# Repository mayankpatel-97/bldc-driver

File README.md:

# BLDC Driver

## Overview
This project is an open-source BLDC motor driver designed for drone applications. It implements a sensorless control method using **Back EMF** for efficient and precise motor control.

## Motor Control Methods
There are multiple ways to drive a BLDC motor. The three most common methods are:

1. **Hall Sensor-Based Control**  
   - Uses **hall effect sensors** in the motor to detect rotor position.
   - Suitable for applications requiring high precision.

2. **Back EMF-Based Control (Sensorless)**  
   - Most **common in drone ESCs** (Electronic Speed Controllers).
   - Detects rotor position by measuring **Back EMF voltage** on the floating phase.
   - Eliminates the need for sensors, reducing cost and complexity.

3. **Power Control Mode**  
   - Uses **shunt resistors** to monitor **current in each phase**.
   - Enables precise **torque and power control**.
   - Required for advanced techniques like **Field-Oriented Control (FOC)**.

## Current Implementation
- **Control Method**: Back EMF sensing (sensorless)  
- **Target Application**: Drone ESC

## Future Enhancements
- **CAN Bus Interface** for communication
- **UART Interface** for debugging and configuration
- In the next varient, one board would have the driver for all the 4 motors required for quad copter.

## PCB information 
- Generated gerber files are in gerber folder of the project directory
- PCB file size: 54x29 mm.

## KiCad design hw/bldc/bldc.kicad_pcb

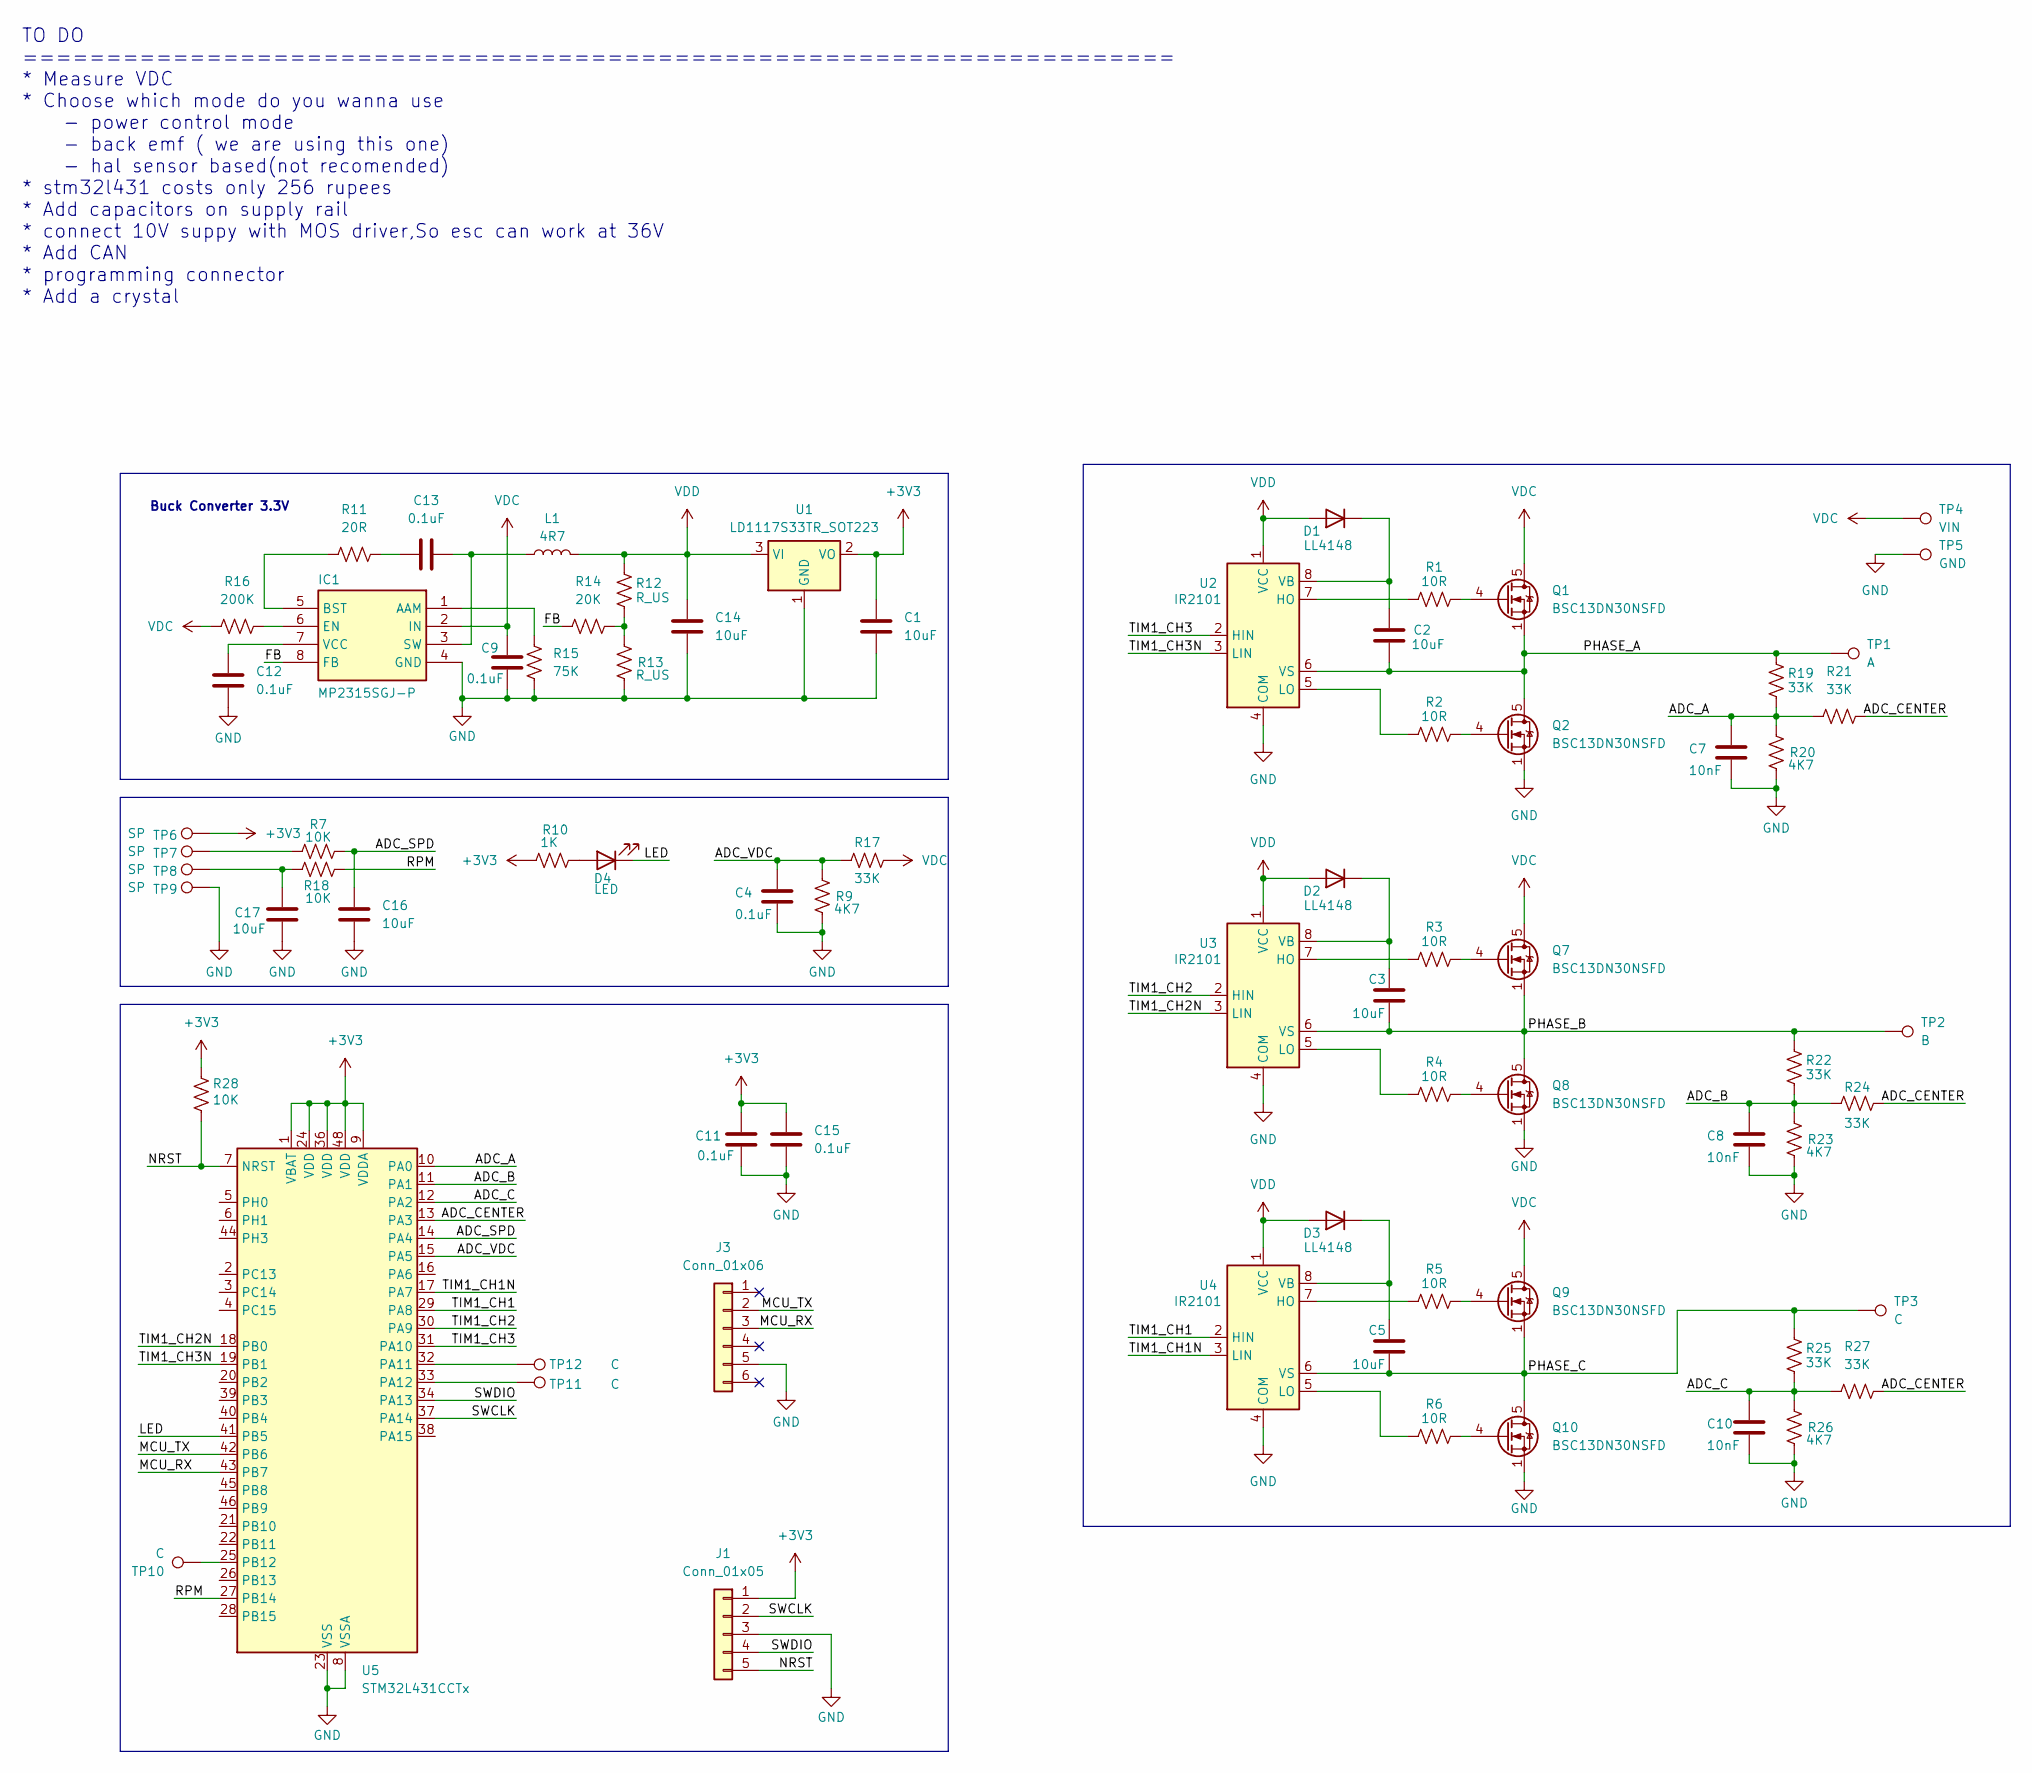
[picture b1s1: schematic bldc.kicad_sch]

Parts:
C1, C2, C3, C5, C14, C16, C17: 10uF; C_0603_1608Metric
C4, C9, C11, C12, C13, C15: 0.1uF; C_0603_1608Metric
C7, C8, C10: 10nF; C_0603_1608Metric
D1, D2, D3: LL4148; D_MiniMELF
D4: LED; LED_0603_1608Metric
IC1: MP2315SGJ-P; MP2315SGJ; Manufacturer_Part_Number MP2315SGJ-P; Mouser Part Number 946-MP2315SGJ-P
J1: Conn_01x05; PinHeader_1x05_P2.00mm_Vertical
J3: Conn_01x06; PinHeader_1x06_P2.54mm_Vertical
L1: 4R7; L_Neosid_SM-PIC0512H
Q1, Q2, Q7, Q8, Q9, Q10: BSC13DN30NSFD; TDSON-8-1
R1, R2, R3, R4, R5, R6: 10R; R_0603_1608Metric
R7, R18, R28: 10K; R_0603_1608Metric
R9, R20, R23, R26: 4K7; R_0603_1608Metric
R10: 1K; R_0603_1608Metric
R11: 20R; R_0603_1608Metric
R12, R13: R_US; R_0603_1608Metric
R14: 20K; R_0603_1608Metric
R15: 75K; R_0603_1608Metric
R16: 200K; R_0603_1608Metric
R17, R19, R21, R22, R24, R25, R27: 33K; R_0603_1608Metric
TP1: A; SOLDERPAD6x4
TP2: B; SOLDERPAD6x4
TP3: C; SOLDERPAD6x4
TP4: VIN; SOLDERPAD6x4
TP5: GND; SOLDERPAD6x4
TP6, TP7, TP8, TP9: SP; TestPoint_Pad_3.0x3.0mm
TP10, TP11, TP12: C; TestPoint_Pad_D1.0mm
U1: LD1117S33TR_SOT223; SOT-223-3_TabPin2
U2, U3, U4: IR2101; SOIC-8_3.9x4.9mm_P1.27mm
U5: STM32L431CCTx; LQFP-48_7x7mm_P0.5mm

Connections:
+3V3: C1.2, C11.2, C15.2, J1.1, R10.1, R28.2, TP6.1, U1.2 (VO), U5.1 (VBAT), U5.9 (VDDA), U5.24 (VDD), U5.36 (VDD), U5.48 (VDD)
/ADC_A: C7.1, R19.2, R20.1, R21.1, U5.10 (PA0)
/ADC_B: C8.1, R22.2, R23.1, R24.1, U5.11 (PA1)
/ADC_C: C10.1, R25.2, R26.1, R27.1, U5.12 (PA2)
/ADC_CENTER: R21.2, R24.2, R27.2, U5.13 (PA3)
/ADC_SPD: C16.2, R18.1, U5.14 (PA4)
/ADC_VDC: C4.1, R9.1, R17.1, U5.15 (PA5)
/FB: IC1.8 (FB), R14.1
/LED: D4.1 (K), U5.41 (PB5)
/MCU_RX: J3.3, U5.43 (PB7)
/MCU_TX: J3.2, U5.42 (PB6)
/NRST: J1.5, R28.1, U5.7 (NRST)
/PHASE_A: C2.2, Q1.1 (S), Q1.2 (S), Q1.3 (S), Q2.5 (D), R19.1, TP1.1, U2.6 (VS)
/PHASE_B: C3.2, Q7.1 (S), Q7.2 (S), Q7.3 (S), Q8.5 (D), R22.1, TP2.1, U3.6 (VS)
/PHASE_C: C5.2, Q9.1 (S), Q9.2 (S), Q9.3 (S), Q10.5 (D), R25.1, TP3.1, U4.6 (VS)
/RPM: R7.1, U5.27 (PB14)
/SWCLK: J1.2, U5.37 (PA14)
/SWDIO: J1.4, U5.34 (PA13)
/TIM1_CH1: U4.2 (HIN), U5.29 (PA8)
/TIM1_CH1N: U4.3 (LIN), U5.17 (PA7)
/TIM1_CH2: U3.2 (HIN), U5.30 (PA9)
/TIM1_CH2N: U3.3 (LIN), U5.18 (PB0)
/TIM1_CH3: U2.2 (HIN), U5.31 (PA10)
/TIM1_CH3N: U2.3 (LIN), U5.19 (PB1)
GND: C1.1, C4.2, C7.2, C8.2, C9.2, C10.2, C11.1, C12.2, C14.1, C15.1, C16.1, C17.1, IC1.4 (GND), J1.3, J3.5, Q2.1 (S), Q2.2 (S), Q2.3 (S), Q8.1 (S), Q8.2 (S), Q8.3 (S), Q10.1 (S), Q10.2 (S), Q10.3 (S), R9.2, R13.2, R15.2, R20.2, R23.2, R26.2, TP5.1, TP9.1, U1.1 (GND), U2.4 (COM), U3.4 (COM), U4.4 (COM), U5.8 (VSSA), U5.23 (VSS), U5.35 (VSS), U5.47 (VSS)
unnamed: C13.1, R11.2
unnamed: C17.2, R7.2, TP8.1
unnamed: C2.1, D1.1 (K), U2.8 (VB)
unnamed: C3.1, D2.1 (K), U3.8 (VB)
unnamed: C5.1, D3.1 (K), U4.8 (VB)
unnamed: D4.2 (A), R10.2
unnamed: IC1.1 (AAM), R15.1
unnamed: IC1.5 (BST), R11.1
unnamed: IC1.6 (EN), R16.2
unnamed: C13.2, IC1.3 (SW), L1.1
unnamed: C12.1, IC1.7 (VCC)
unnamed: Q1.4 (G), R1.2
unnamed: Q2.4 (G), R2.2
unnamed: Q7.4 (G), R3.2
unnamed: Q8.4 (G), R4.2
unnamed: Q9.4 (G), R5.2
unnamed: Q10.4 (G), R6.2
unnamed: R12.2, R13.1, R14.2
unnamed: R18.2, TP7.1
unnamed: R1.1, U2.7 (HO)
unnamed: R2.1, U2.5 (LO)
unnamed: R3.1, U3.7 (HO)
unnamed: R4.1, U3.5 (LO)
unnamed: R5.1, U4.7 (HO)
unnamed: R6.1, U4.5 (LO)
unnamed: TP12.1, U5.32 (PA11)
unnamed: TP11.1, U5.33 (PA12)
unnamed: TP10.1, U5.25 (PB12)
VDC: C9.1, IC1.2 (IN), Q1.5 (D), Q7.5 (D), Q9.5 (D), R16.1, R17.2, TP4.1
VDD: C14.2, D1.2 (A), D2.2 (A), D3.2 (A), L1.2, R12.1, U1.3 (VI), U2.1 (VCC), U3.1 (VCC), U4.1 (VCC)

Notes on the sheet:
TO DO ===================================================================== * Measure VDC * Choose which mode do you wanna use - power control mode - back emf ( we are using this one) - hal sensor based(not recomended) * stm32l431 costs only 256 rupees * Add capacitors on supply rail * connect 10V 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
Buck Converter 3.3V

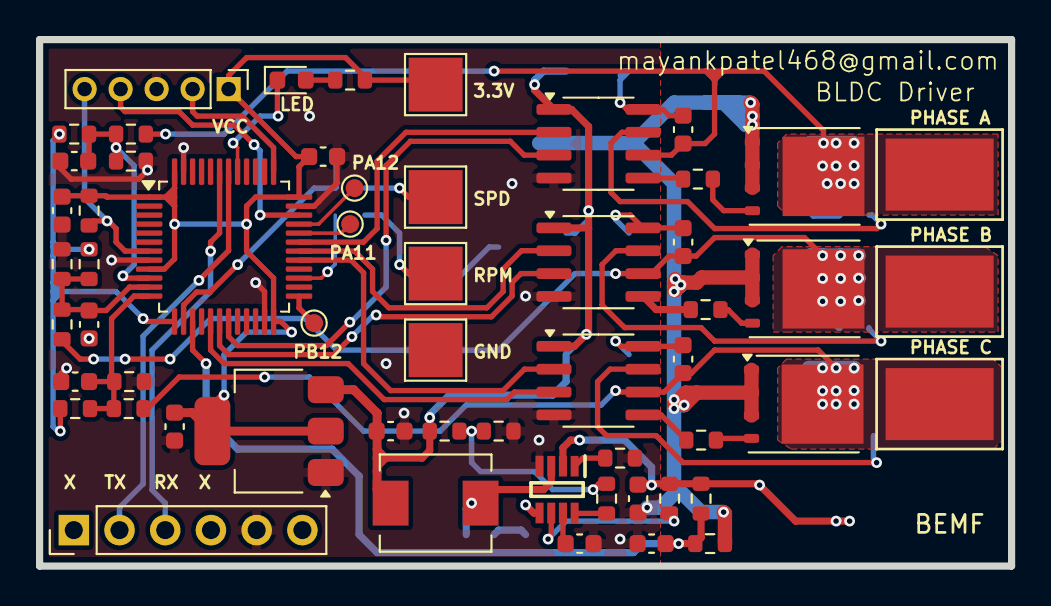
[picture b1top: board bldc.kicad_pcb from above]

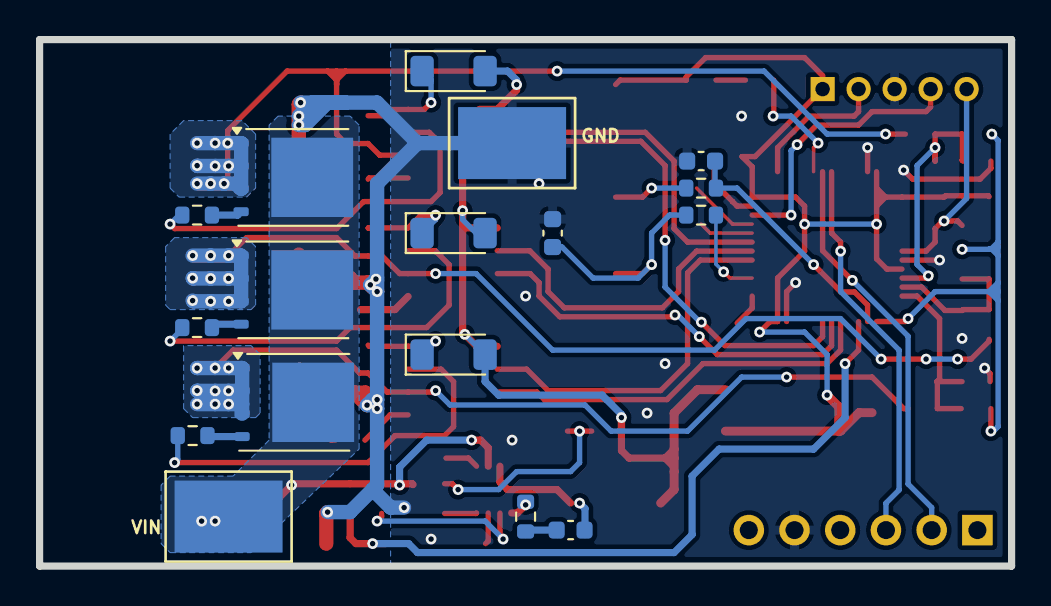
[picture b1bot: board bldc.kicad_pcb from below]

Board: 2 copper layers, 54.0 x 29.2 mm, 74 parts (17 on the bottom side), 55 nets.

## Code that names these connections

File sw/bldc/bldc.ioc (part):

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Mcu.Name=STM32L431C(B-C)Tx
Mcu.Package=LQFP48
Mcu.UserName=STM32L431CCTx
PA0.Signal=ADCx_IN5
PA1.Signal=ADCx_IN6
PA10.Signal=S_TIM1_CH3
PA13\ (JTMS-SWDIO).Mode=Serial_Wire
PA13\ (JTMS-SWDIO).Signal=SYS_JTMS-SWDIO
PA14\ (JTCK-SWCLK).Mode=Serial_Wire
PA14\ (JTCK-SWCLK).Signal=SYS_JTCK-SWCLK
PA2.Signal=ADCx_IN7
PA3.Signal=ADCx_IN8
PA4.Signal=ADCx_IN9
PA7.GPIOParameters=GPIO_Label
PA7.GPIO_Label=PHASE_A_L
PA7.Signal=GPIO_Output
PA8.Signal=S_TIM1_CH1
PA9.Signal=S_TIM1_CH2
PB0.GPIOParameters=GPIO_Label
PB0.GPIO_Label=PHASE_B_L
PB0.Signal=GPIO_Output
PB1.GPIOParameters=GPIO_Label
PB1.GPIO_Label=PHASE_C_L
PB1.Signal=GPIO_Output
PB14.Signal=S_TIM15_CH1
PB5.GPIOParameters=GPIO_Label
PB5.GPIO_Label=LED
PB5.Signal=GPIO_Output
PB6.Mode=Asynchronous
PB6.Signal=USART1_TX
PB7.Mode=Asynchronous
PB7.Signal=USART1_RX
RCC.HSE_VALUE=8000000
RCC.SYSCLKFreq_VALUE=32000000
RCC.SYSCLKSource=RCC_SYSCLKSOURCE_PLLCLK
board=custom

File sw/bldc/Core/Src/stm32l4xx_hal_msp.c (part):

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
    __HAL_RCC_GPIOA_CLK_ENABLE();
    /**ADC1 GPIO Configuration
    PA0     ------> ADC1_IN5
    PA1     ------> ADC1_IN6
    PA2     ------> ADC1_IN7
    PA3     ------> ADC1_IN8
    PA4     ------> ADC1_IN9
    */
    GPIO_InitStruct.Pin = GPIO_PIN_0|GPIO_PIN_1|GPIO_PIN_2|GPIO_PIN_3
                          |GPIO_PIN_4;
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    __HAL_RCC_ADC_CLK_DISABLE();

    /**ADC1 GPIO Configuration
    PA0     ------> ADC1_IN5
    PA1     ------> ADC1_IN6
    PA2     ------> ADC1_IN7
    PA3     ------> ADC1_IN8
    PA4     ------> ADC1_IN9
    */
    HAL_GPIO_DeInit(GPIOA, GPIO_PIN_0|GPIO_PIN_1|GPIO_PIN_2|GPIO_PIN_3
                          |GPIO_PIN_4);
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  /* USER CODE END TIM1_MspPostInit 0 */
    __HAL_RCC_GPIOA_CLK_ENABLE();
    /**TIM1 GPIO Configuration
    PA8     ------> TIM1_CH1
    PA9     ------> TIM1_CH2
    PA10     ------> TIM1_CH3
    */
    GPIO_InitStruct.Pin = GPIO_PIN_8|GPIO_PIN_9|GPIO_PIN_10;
    GPIO_InitStruct.Mode = GPIO_MODE_AF_PP;
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
    __HAL_RCC_GPIOB_CLK_ENABLE();
    /**TIM15 GPIO Configuration
    PB14     ------> TIM15_CH1
    */
    GPIO_InitStruct.Pin = GPIO_PIN_14;
    GPIO_InitStruct.Mode = GPIO_MODE_AF_PP;
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
    __HAL_RCC_GPIOB_CLK_ENABLE();
    /**USART1 GPIO Configuration
    PB6     ------> USART1_TX
    PB7     ------> USART1_RX
    */
    GPIO_InitStruct.Pin = GPIO_PIN_6|GPIO_PIN_7;
    GPIO_InitStruct.Mode = GPIO_MODE_AF_PP;
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    __HAL_RCC_USART1_CLK_DISABLE();

    /**USART1 GPIO Configuration
    PB6     ------> USART1_TX
    PB7     ------> USART1_RX
    */
    HAL_GPIO_DeInit(GPIOB, GPIO_PIN_6|GPIO_PIN_7);

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
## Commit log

2025-03-14 added kicad project
2025-03-14 schematic
2025-03-14 schematic update
2025-03-14 sch update
2025-03-14 sch update using BEMF
2025-03-15 pcb update
2025-03-16 component placement
2025-03-16 pcb routing update
2025-03-16 Gerber Generated
2025-03-17 made some corrections
2025-03-20 added sw
2025-03-20 sw update
2025-03-20 added gitignore
2025-03-20 removed settings
2025-03-22 added pcb pic in README.md

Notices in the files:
sw/bldc/Core/Src/stm32l4xx_hal_msp.c:
Copyright (c) 2025 STMicroelectronics.
All rights reserved.
This software is licensed under terms that can be found in the LICENSE file
